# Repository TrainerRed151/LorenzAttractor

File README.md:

# LorenzAttractor

Based on <https://seti.harvard.edu/unusual_stuff/misc/lorenz.htm>

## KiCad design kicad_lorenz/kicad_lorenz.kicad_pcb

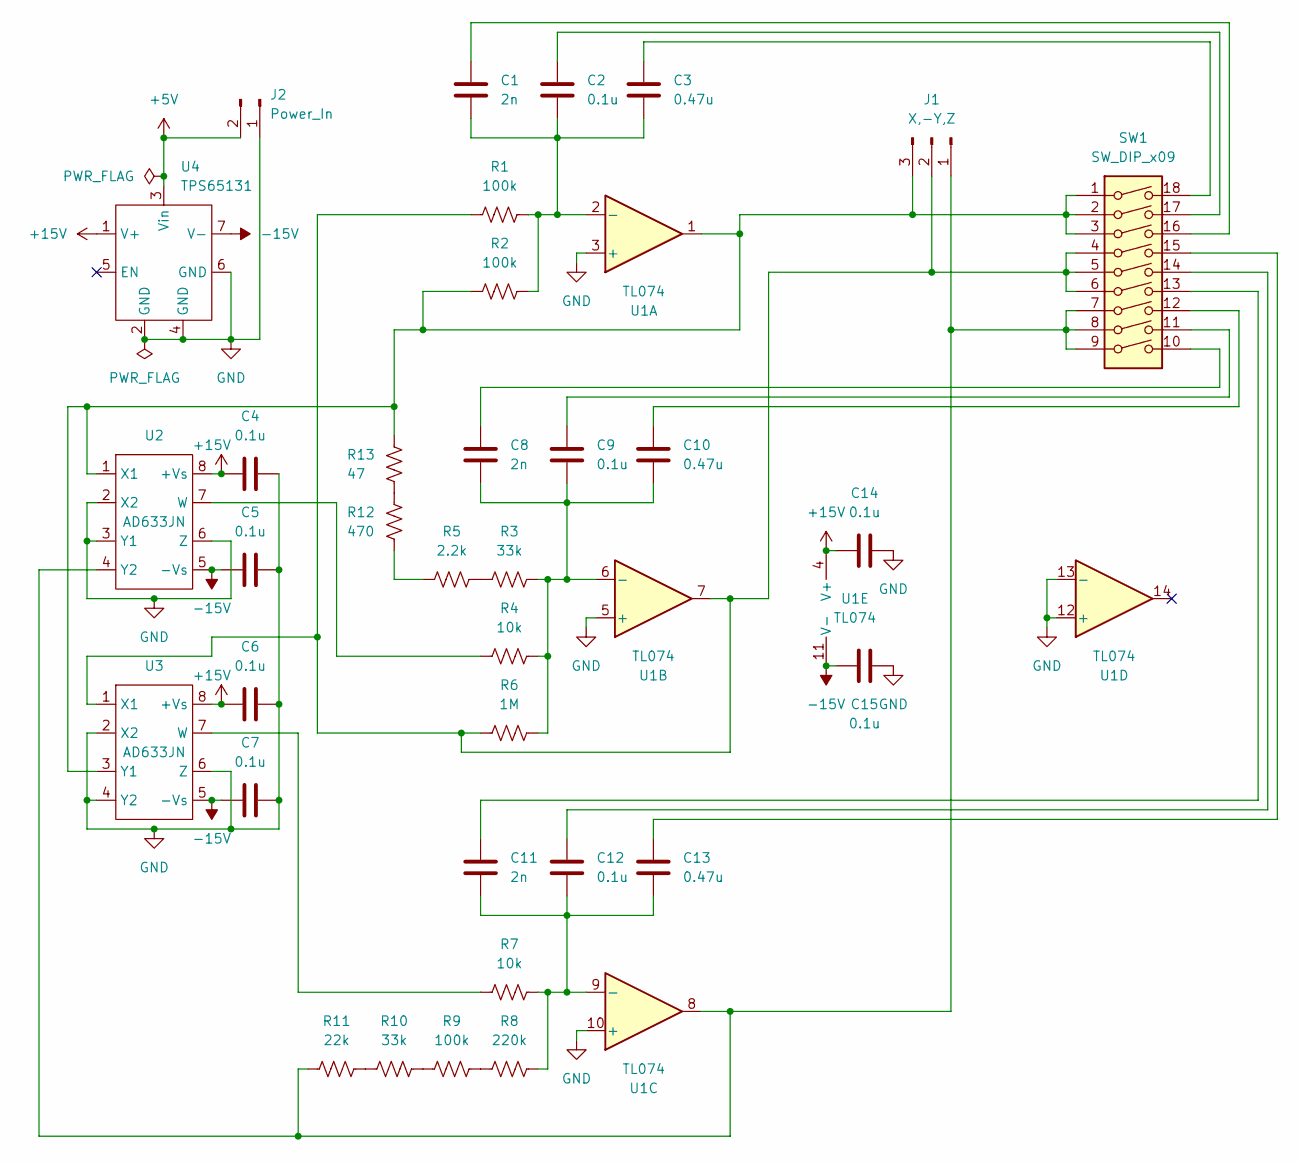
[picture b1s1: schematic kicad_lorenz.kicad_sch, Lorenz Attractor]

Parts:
C1, C8, C11: 2n; C_Disc_D5.0mm_W2.5mm_P2.50mm
C2, C4, C5, C6, C7, C9, C12, C14, C15: 0.1u; C_Disc_D5.0mm_W2.5mm_P2.50mm
C3, C10, C13: 0.47u; C_Disc_D5.0mm_W2.5mm_P2.50mm
J1: X,-Y,Z; SolderWire-0.5sqmm_1x03_P4.8mm_D0.9mm_OD2.3mm
J2: Power_In; SolderWire-0.5sqmm_1x02_P4.8mm_D0.9mm_OD2.3mm
R1, R2, R9: 100k; R_Axial_DIN0207_L6.3mm_D2.5mm_P10.16mm_Horizontal
R3, R10: 33k; R_Axial_DIN0207_L6.3mm_D2.5mm_P10.16mm_Horizontal
R4, R7: 10k; R_Axial_DIN0207_L6.3mm_D2.5mm_P10.16mm_Horizontal
R5: 2.2k; R_Axial_DIN0207_L6.3mm_D2.5mm_P10.16mm_Horizontal
R6: 1M; R_Axial_DIN0207_L6.3mm_D2.5mm_P10.16mm_Horizontal
R8: 220k; R_Axial_DIN0207_L6.3mm_D2.5mm_P10.16mm_Horizontal
R11: 22k; R_Axial_DIN0207_L6.3mm_D2.5mm_P10.16mm_Horizontal
R12: 470; R_Axial_DIN0207_L6.3mm_D2.5mm_P10.16mm_Horizontal
R13: 47; R_Axial_DIN0207_L6.3mm_D2.5mm_P10.16mm_Horizontal
SW1: SW_DIP_x09; DIP-18_W7.62mm_Socket
U1: TL074; DIP-14_W7.62mm
U2, U3: AD633JN; DIP-8_W7.62mm
U4: TPS65131

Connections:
+5V: J2.2, U4.3 (Vin); also elsewhere on the board
+15V: C4.1, C6.1, C14.1, U1.4 (V+), U2.8 (+Vs), U3.8 (+Vs), U4.1 (V+)
-15V: C5.1, C7.1, C15.1, U1.11 (V-), U2.5 (-Vs), U3.5 (-Vs), U4.7 (V-)
GND: C4.2, C5.2, C6.2, C7.2, C14.2, C15.2, J2.1, U1.3 (+), U1.5 (+), U1.10 (+), U1.12 (+), U1.13 (-), U2.2 (X2), U2.3 (Y1), U2.6 (Z), U3.2 (X2), U3.4 (Y2), U3.6 (Z), U4.2 (GND), U4.4 (GND), U4.6 (GND); also elsewhere on the board
unnamed: C1.1, SW1.16
unnamed: C2.1, SW1.17
unnamed: C3.1, SW1.18
unnamed: C8.1, SW1.10
unnamed: C9.1, SW1.11
unnamed: C10.1, SW1.12
unnamed: C11.1, SW1.13
unnamed: C12.1, SW1.14
unnamed: C13.1, SW1.15
unnamed 13: J1.1, R11.1, SW1.7, SW1.8, SW1.9, U1.8, U2.4 (Y2); also elsewhere on the board
unnamed 14: J1.2, R1.1, R6.1, SW1.4, SW1.5, SW1.6, U1.7, U3.1 (X1); also elsewhere on the board
unnamed 15: J1.3, R2.1, R13.2, SW1.1, SW1.2, SW1.3, U1.1, U2.1 (X1), U3.3 (Y1); also elsewhere on the board
unnamed: R3.1, R5.2
unnamed: R8.1, R9.2
unnamed: R10.1, R11.2
unnamed: R9.1, R10.2
unnamed: R5.1, R12.1
unnamed: R12.2, R13.1
unnamed: C1.2, C2.2, C3.2, R1.2, R2.2, U1.2 (-)
unnamed: C8.2, C9.2, C10.2, R3.2, R4.2, R6.2, U1.6 (-)
unnamed: C11.2, C12.2, C13.2, R7.2, R8.2, U1.9 (-)
unnamed: R4.1, U2.7 (W)
unnamed: R7.1, U3.7 (W)

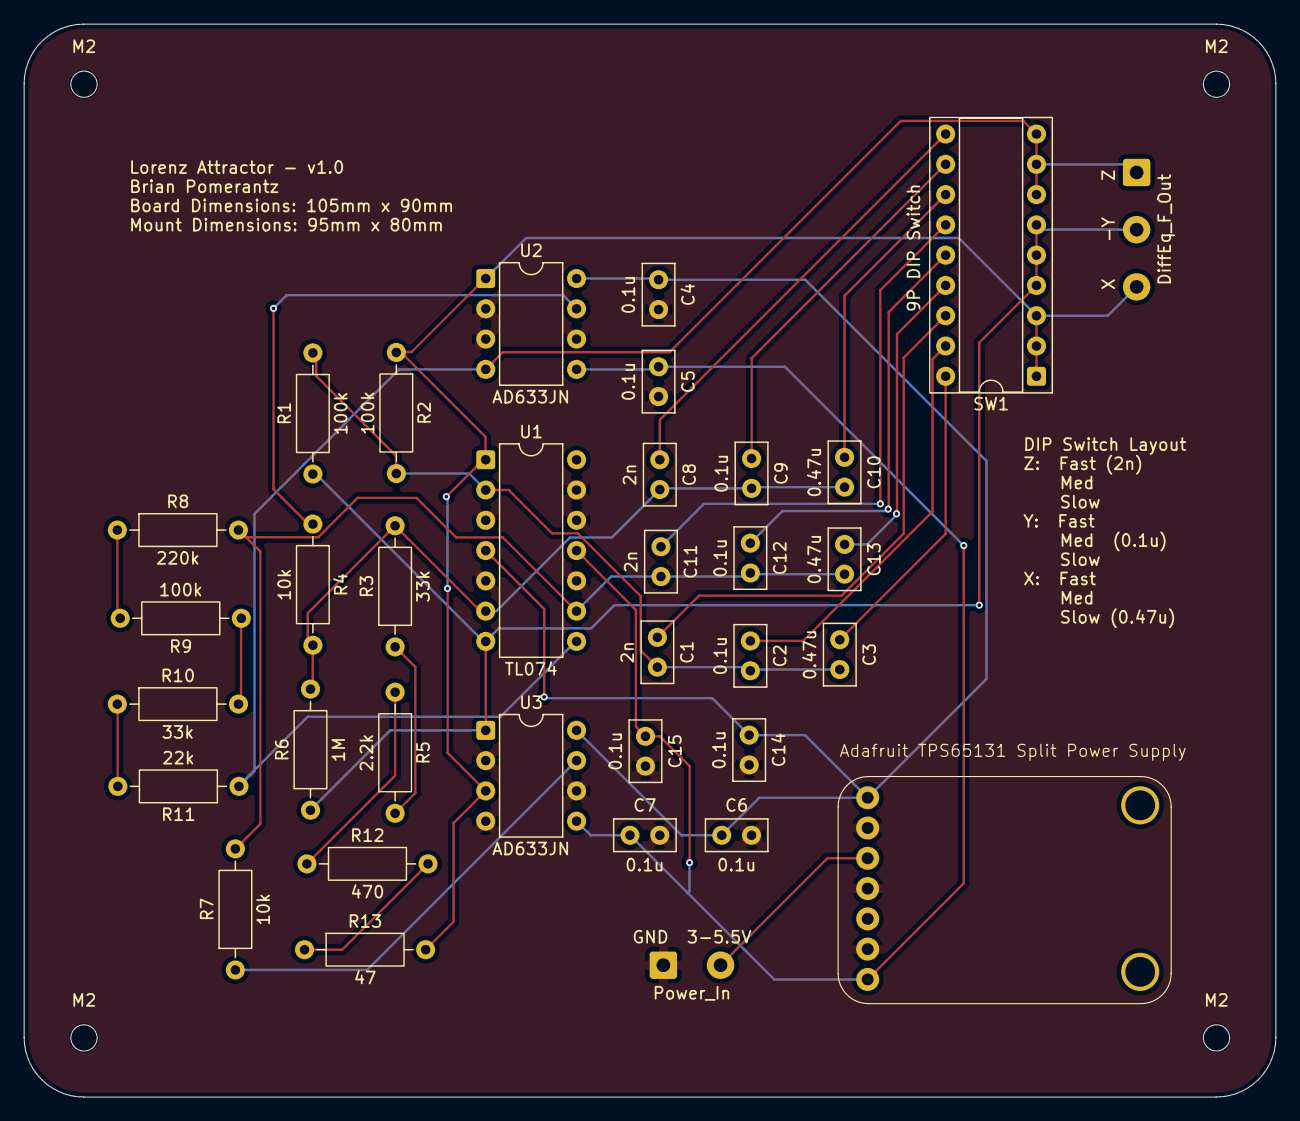
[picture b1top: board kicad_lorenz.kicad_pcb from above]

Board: 2 copper layers, 105.0 x 90.0 mm, 39 parts (0 on the bottom side), 27 nets.

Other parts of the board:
DiffEq_F_Out: X -Y Z; SolderWire-0.5sqmm_1x03_P4.8mm_D0.9mm_OD2.3mm
GND  3-5.5V: Power_In; SolderWire-0.5sqmm_1x02_P4.8mm_D0.9mm_OD2.3mm
M2, M2#2, M2#3, M2#4: MountingHole_2.2mm_M2

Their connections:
+5V: GND 3-5.5V.2; also elsewhere on the board
GND: GND 3-5.5V.1; also elsewhere on the board
unnamed 13: DiffEq_F_Out.1; also elsewhere on the board
unnamed 14: DiffEq_F_Out.2; also elsewhere on the board
unnamed 15: DiffEq_F_Out.3; also elsewhere on the board

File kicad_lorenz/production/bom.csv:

Designator,Footprint,Quantity,Value,LCSC Part #
"C1, C11, C8",C_Disc_D5.0mm_W2.5mm_P2.50mm,3,2n,
"C10, C13, C3",C_Disc_D5.0mm_W2.5mm_P2.50mm,3,0.47u,
"C12, C14, C15, C2, C4, C5, C6, C7, C9",C_Disc_D5.0mm_W2.5mm_P2.50mm,9,0.1u,
DIFFEQ_F_OUT,SolderWire-0.5sqmm_1x03_P4.8mm_D0.9mm_OD2.3mm,1,X    -Y    Z,
GND  3-5.5V,SolderWire-0.5sqmm_1x02_P4.8mm_D0.9mm_OD2.3mm,1,Power_In,
"R1, R2, R9",R_Axial_DIN0207_L6.3mm_D2.5mm_P10.16mm_Horizontal,3,100k,
"R10, R3",R_Axial_DIN0207_L6.3mm_D2.5mm_P10.16mm_Horizontal,2,33k,
R11,R_Axial_DIN0207_L6.3mm_D2.5mm_P10.16mm_Horizontal,1,22k,
R12,R_Axial_DIN0207_L6.3mm_D2.5mm_P10.16mm_Horizontal,1,470,
R13,R_Axial_DIN0207_L6.3mm_D2.5mm_P10.16mm_Horizontal,1,47,
"R4, R7",R_Axial_DIN0207_L6.3mm_D2.5mm_P10.16mm_Horizontal,2,10k,
R5,R_Axial_DIN0207_L6.3mm_D2.5mm_P10.16mm_Horizontal,1,2.2k,
R6,R_Axial_DIN0207_L6.3mm_D2.5mm_P10.16mm_Horizontal,1,1M,
R8,R_Axial_DIN0207_L6.3mm_D2.5mm_P10.16mm_Horizontal,1,220k,
SW1,DIP-18_W7.62mm_Socket,1,SW_DIP_x09,
U1,DIP-14_W7.62mm,1,TL074,
"U2, U3",DIP-8_W7.62mm,2,AD633JN,
U4,TPS65131,1,TPS65131,

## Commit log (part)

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2026-04-02 python plotter, LTSpice schematic (start)
2026-04-02 Forward Euler method
2026-04-03 full LTSpice schematic
2026-04-03 clean schematic asc file
2026-04-03 reference local AD633 file
2026-04-03 fix signs in AD633 pins
2026-04-03 AD633 reference local cir, plot TSV data
2026-04-23 power capacitors on AD633

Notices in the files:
parts and their libraries:
Copyright 1993, 2012 by Analog Devices
